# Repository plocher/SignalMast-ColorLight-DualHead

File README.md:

# SignalMast-ColorLight-DualHead
## License: CERN Open Hardware Licence v1.2

Low cost Signal Mast - single high head Color Light - N scale

Changes from 1.0D: Top Layer text "GYR+" didn't have "SPIN" set, so it was wrong side up and backward on the top row of upsidedown masts...
(The square pad is "+", no matter what the legend says...)

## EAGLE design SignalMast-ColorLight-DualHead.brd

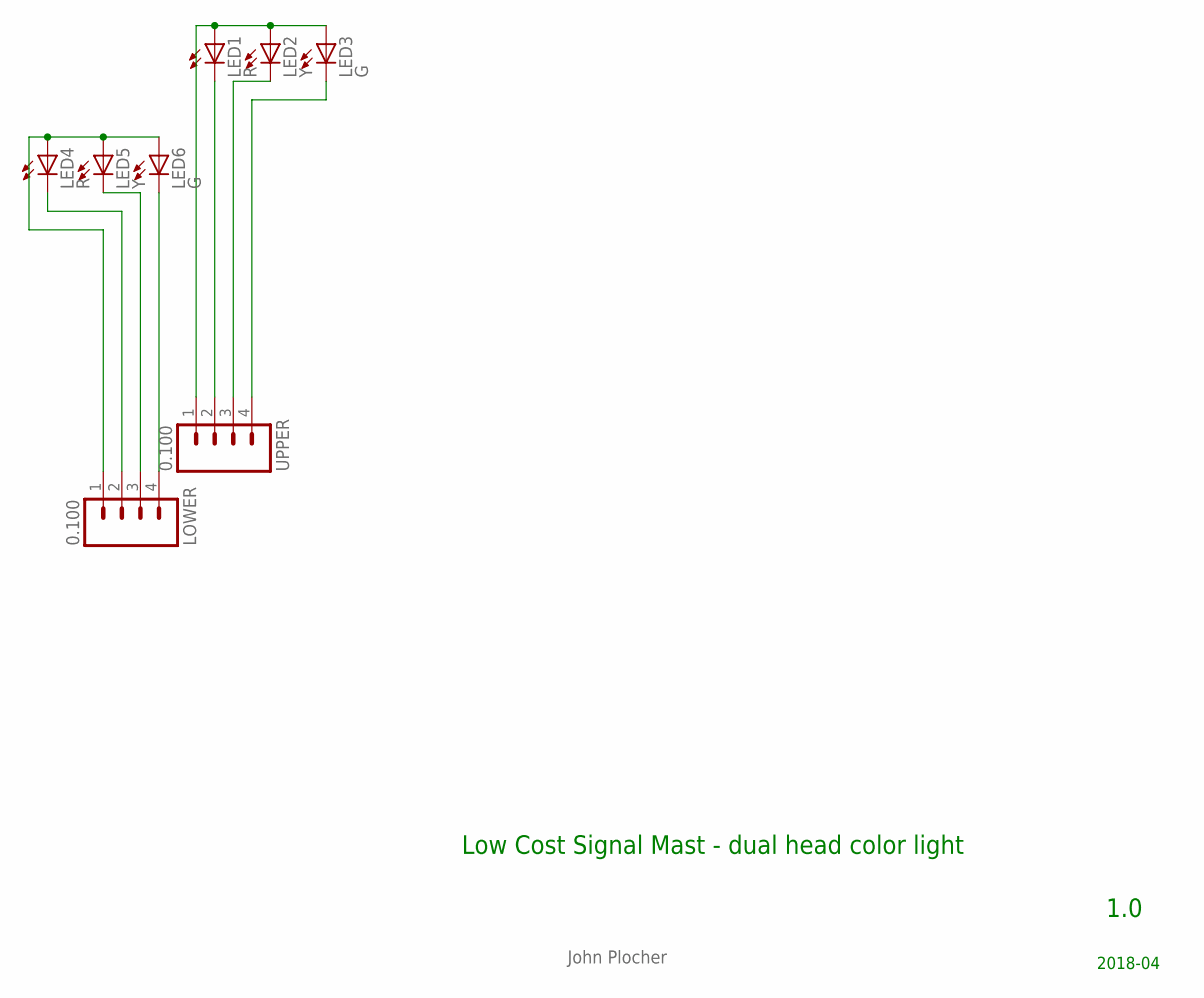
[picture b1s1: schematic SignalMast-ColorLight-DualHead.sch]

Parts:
LED1, LED4: R; 0603-LED
LED2, LED5: Y; 0603-LED
LED3, LED6: G; 0603-LED
LOWER: 0.100; 1X04_LOCK
UPPER: 0.100; 1X04_LOCK

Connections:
AG: LED6.C, LOWER.4
AR: LED4.C, LOWER.2
AV+: LED4.A, LED5.A, LED6.A, LOWER.1
AY: LED5.C, LOWER.3
BG: LED3.C, UPPER.4
BR: LED1.C, UPPER.2
BV+: LED1.A, LED2.A, LED3.A, UPPER.1
BY: LED2.C, UPPER.3

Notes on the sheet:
1.0
2018-04
Low Cost Signal Mast - dual head color light
John Plocher

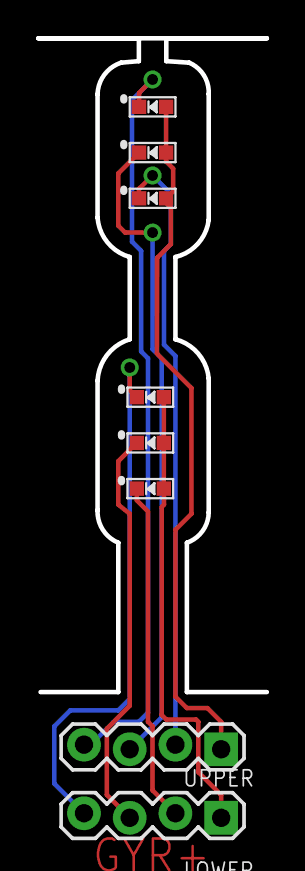
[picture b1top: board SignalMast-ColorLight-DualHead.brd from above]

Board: 2 copper layers, 8 parts (0 on the bottom side), 8 nets.

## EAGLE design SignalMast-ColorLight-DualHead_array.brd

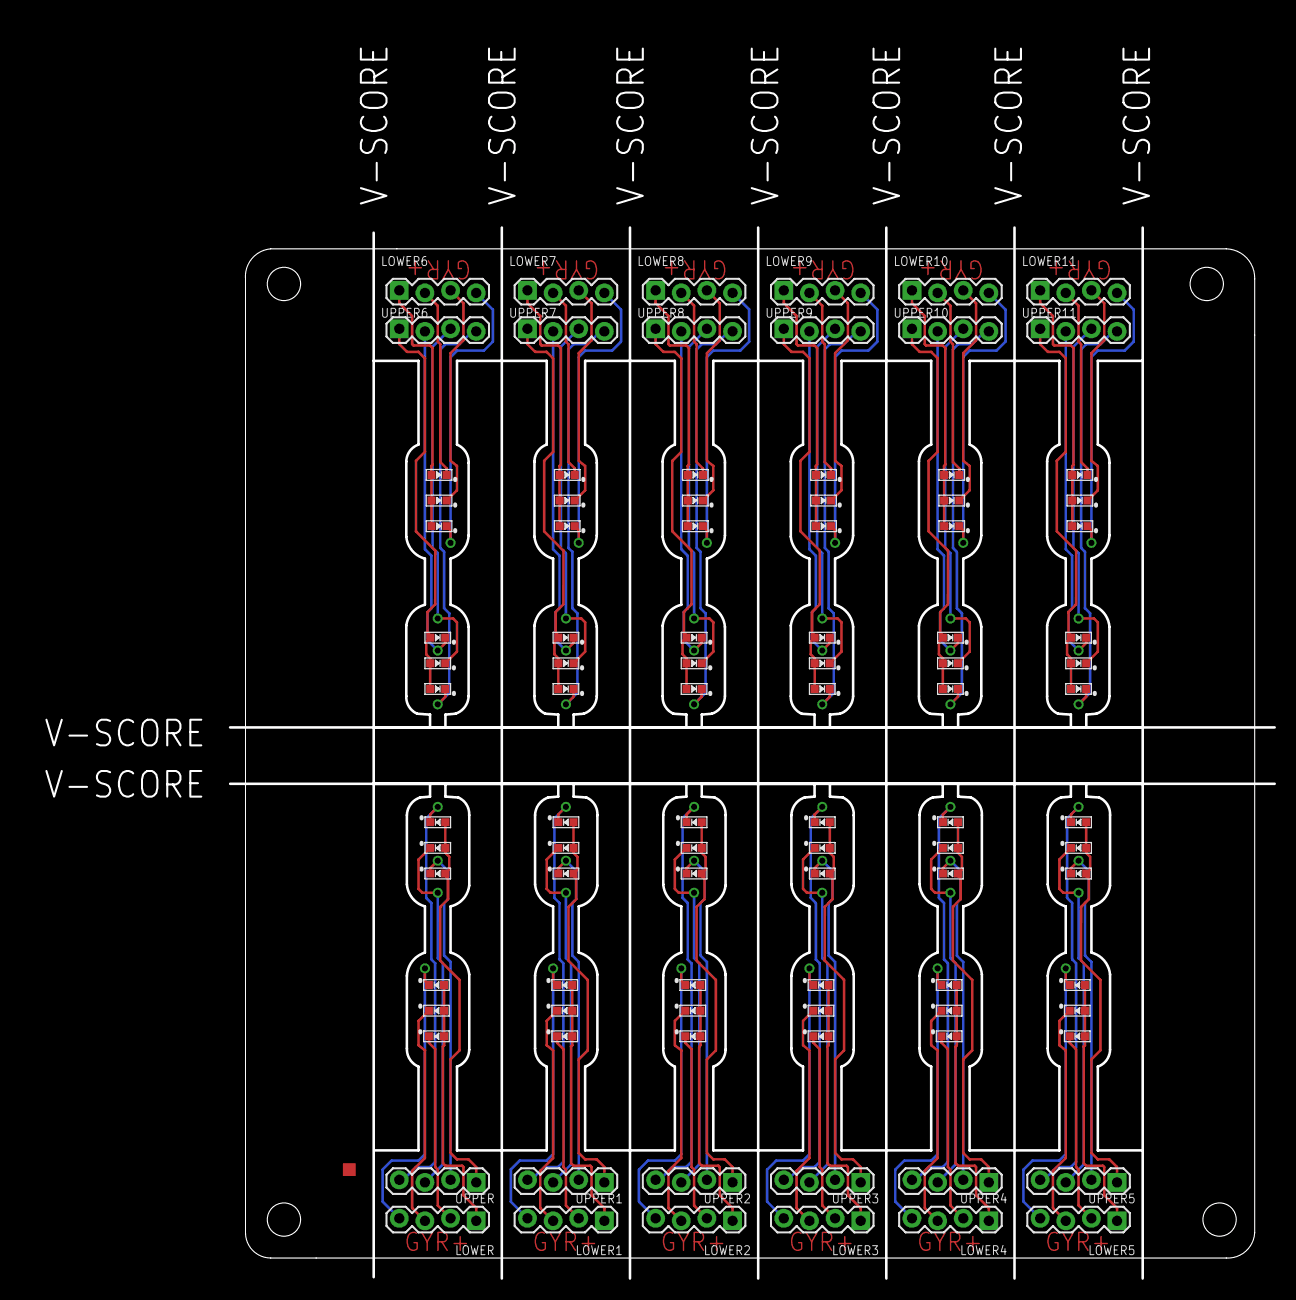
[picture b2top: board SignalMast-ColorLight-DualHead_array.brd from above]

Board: 2 copper layers, 103.5 x 104.1 mm, 97 parts (0 on the bottom side), 96 nets.

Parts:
BOARD1: BOARD; BOARD-SEEED10X10-NOHOLES
LED1, LED4, LED7, LED10, LED13, LED16, LED19, LED22, LED25, LED28, LED31, LED34, LED37, LED40, LED43, LED46, LED49, LED52, LED55, LED58, LED61, LED64, LED67, LED70: R; 0603-LED
LED2, LED5, LED8, LED11, LED14, LED17, LED20, LED23, LED26, LED29, LED32, LED35, LED38, LED41, LED44, LED47, LED50, LED53, LED56, LED59, LED62, LED65, LED68, LED71: Y; 0603-LED
LED3, LED6, LED9, LED12, LED15, LED18, LED21, LED24, LED27, LED30, LED33, LED36, LED39, LED42, LED45, LED48, LED51, LED54, LED57, LED60, LED63, LED66, LED69, LED72: G; 0603-LED
LOWER, LOWER1, LOWER2, LOWER3, LOWER4, LOWER5, LOWER6, LOWER7, LOWER8, LOWER9, LOWER10, LOWER11: 0.100; 1X04_LOCK
UPPER, UPPER1, UPPER2, UPPER3, UPPER4, UPPER5, UPPER6, UPPER7, UPPER8, UPPER9, UPPER10, UPPER11: 0.100; 1X04_LOCK

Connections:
AG: LED6.C, LOWER.4
AG1: LED12.C, LOWER1.4
AG2: LED18.C, LOWER2.4
AG3: LED24.C, LOWER3.4
AG4: LED30.C, LOWER4.4
AG5: LED36.C, LOWER5.4
AG6: LED42.C, LOWER6.4
AG7: LED48.C, LOWER7.4
AG8: LED54.C, LOWER8.4
AG9: LED60.C, LOWER9.4
AG10: LED66.C, LOWER10.4
AG11: LED72.C, LOWER11.4
AR: LED4.C, LOWER.2
AR1: LED10.C, LOWER1.2
AR2: LED16.C, LOWER2.2
AR3: LED22.C, LOWER3.2
AR4: LED28.C, LOWER4.2
AR5: LED34.C, LOWER5.2
AR6: LED40.C, LOWER6.2
AR7: LED46.C, LOWER7.2
AR8: LED52.C, LOWER8.2
AR9: LED58.C, LOWER9.2
AR10: LED64.C, LOWER10.2
AR11: LED70.C, LOWER11.2
AV+: LED4.A, LED5.A, LED6.A, LOWER.1
AV+1: LED10.A, LED11.A, LED12.A, LOWER1.1
AV+2: LED16.A, LED17.A, LED18.A, LOWER2.1
AV+3: LED22.A, LED23.A, LED24.A, LOWER3.1
AV+4: LED28.A, LED29.A, LED30.A, LOWER4.1
AV+5: LED34.A, LED35.A, LED36.A, LOWER5.1
AV+6: LED40.A, LED41.A, LED42.A, LOWER6.1
AV+7: LED46.A, LED47.A, LED48.A, LOWER7.1
AV+8: LED52.A, LED53.A, LED54.A, LOWER8.1
AV+9: LED58.A, LED59.A, LED60.A, LOWER9.1
AV+10: LED64.A, LED65.A, LED66.A, LOWER10.1
AV+11: LED70.A, LED71.A, LED72.A, LOWER11.1
AY: LED5.C, LOWER.3
AY1: LED11.C, LOWER1.3
AY2: LED17.C, LOWER2.3
AY3: LED23.C, LOWER3.3
AY4: LED29.C, LOWER4.3
AY5: LED35.C, LOWER5.3
AY6: LED41.C, LOWER6.3
AY7: LED47.C, LOWER7.3
AY8: LED53.C, LOWER8.3
AY9: LED59.C, LOWER9.3
AY10: LED65.C, LOWER10.3
AY11: LED71.C, LOWER11.3
BG: LED3.C, UPPER.4
BG1: LED9.C, UPPER1.4
BG2: LED15.C, UPPER2.4
BG3: LED21.C, UPPER3.4
BG4: LED27.C, UPPER4.4
BG5: LED33.C, UPPER5.4
BG6: LED39.C, UPPER6.4
BG7: LED45.C, UPPER7.4
BG8: LED51.C, UPPER8.4
BG9: LED57.C, UPPER9.4
BG10: LED63.C, UPPER10.4
BG11: LED69.C, UPPER11.4
BR: LED1.C, UPPER.2
BR1: LED7.C, UPPER1.2
BR2: LED13.C, UPPER2.2
BR3: LED19.C, UPPER3.2
BR4: LED25.C, UPPER4.2
BR5: LED31.C, UPPER5.2
BR6: LED37.C, UPPER6.2
BR7: LED43.C, UPPER7.2
BR8: LED49.C, UPPER8.2
BR9: LED55.C, UPPER9.2
BR10: LED61.C, UPPER10.2
BR11: LED67.C, UPPER11.2
BV+: LED1.A, LED2.A, LED3.A, UPPER.1
BV+1: LED7.A, LED8.A, LED9.A, UPPER1.1
BV+2: LED13.A, LED14.A, LED15.A, UPPER2.1
BV+3: LED19.A, LED20.A, LED21.A, UPPER3.1
BV+4: LED25.A, LED26.A, LED27.A, UPPER4.1
BV+5: LED31.A, LED32.A, LED33.A, UPPER5.1
BV+6: LED37.A, LED38.A, LED39.A, UPPER6.1
BV+7: LED43.A, LED44.A, LED45.A, UPPER7.1
BV+8: LED49.A, LED50.A, LED51.A, UPPER8.1
BV+9: LED55.A, LED56.A, LED57.A, UPPER9.1
BV+10: LED61.A, LED62.A, LED63.A, UPPER10.1
BV+11: LED67.A, LED68.A, LED69.A, UPPER11.1
BY: LED2.C, UPPER.3
BY1: LED8.C, UPPER1.3
BY2: LED14.C, UPPER2.3
BY3: LED20.C, UPPER3.3
BY4: LED26.C, UPPER4.3
BY5: LED32.C, UPPER5.3
BY6: LED38.C, UPPER6.3
BY7: LED44.C, UPPER7.3
BY8: LED50.C, UPPER8.3
BY9: LED56.C, UPPER9.3
BY10: LED62.C, UPPER10.3
BY11: LED68.C, UPPER11.3

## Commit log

2019-12-07 added graphic
2020-05-04 updated tags
2020-10-06 normalized values
